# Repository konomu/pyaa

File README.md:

# Introducing pyaa!
A thirty key steno keyboard powered by QMK firmware and Plover.

## How do I build it?
To build pyaa, all you need is the following:
* PCB (two halves)
* 30 Kailh Choc switches (PG1350)
* 2 Pro Micros (or its derivatives)
  * **Important:** The Pro Micro's USB must face towards the board on both halves.
* 2 TRRS jacks (MJ-4PP-9 or PJ-320A)
* TRRS cable
* and optionally, 2 reset switches (TVBP06)

Once you have finished building it, you must flash the firmware onto the keyboard with QMK.

## How do I use it?
pyaa is powered by QMK firmware and takes advantage of its stenography, combo, and direct pin implementations. Its firmware is available [here](https://github.com/konomu/qmk_firmware/tree/pyaa/keyboards/pyaa). It functions along with [Plover](https://github.com/openstenoproject/plover), a desktop application developed as a part of the [Open Steno Project](http://www.openstenoproject.org/). 

## About
There are many other steno keyboards out there, all of which allow you to input text at speeds upwards of 200 words per minute with the magic of Plover! (and of course, a bit of practice) In fact, pyaa is heavily inspired by Georgi, which was developed by g Heavy Industries' Jane Bernhardt and is available at [gboards](https://www.gboards.ca/product/georgi). Other options for steno keyboards can be found on [Plover's wiki](https://github.com/openstenoproject/plover/wiki/Supported-Hardware).

The PCB uses a direct pin matrix, where each key is connected to an I/O pin on the microcontroller and ground. This makes it so that soldering diodes onto the pcb is not necessary as with other keyboards, reducing cost slightly. N-key rollover functionality, which is crucial for stenography, is left intact.

## Images

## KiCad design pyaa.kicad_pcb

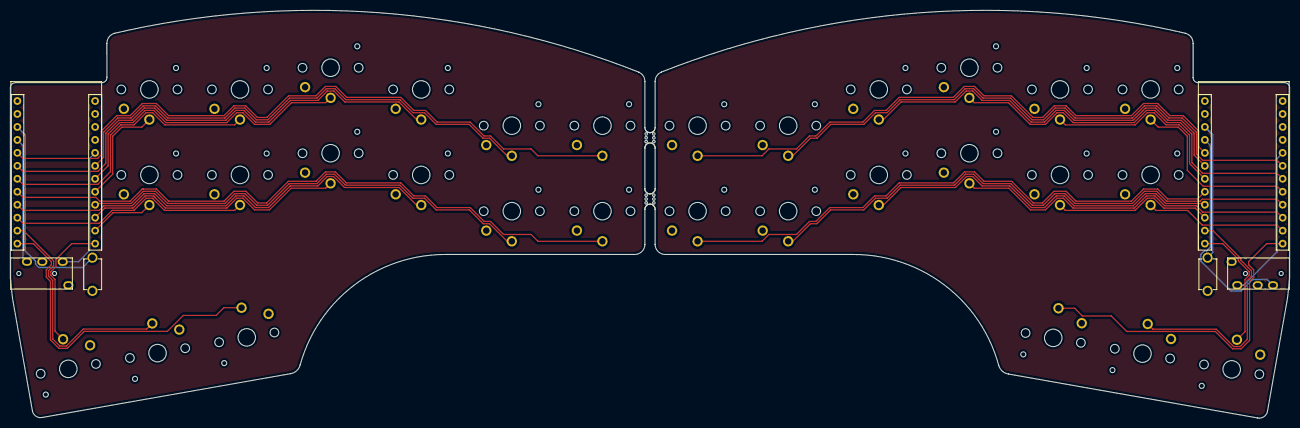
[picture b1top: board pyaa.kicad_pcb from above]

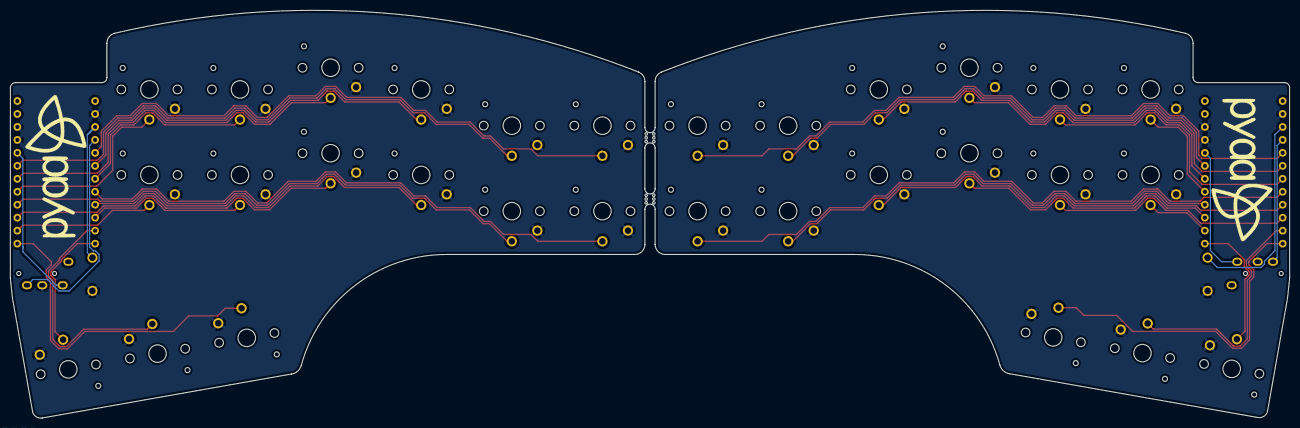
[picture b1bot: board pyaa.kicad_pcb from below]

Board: 2 copper layers, 250.6 x 79.9 mm, 38 parts (2 on the bottom side), 36 nets.

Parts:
J1, J2: MJ-4PP-9; TRRS-PJ-320A
K0, K1: KEYSW; Choc_PG1350_Choc_Spacing
KA1: KEYSW; Choc_PG1350_Choc_Spacing
KBR1: KEYSW; Choc_PG1350_Choc_Spacing
KDR1: KEYSW; Choc_PG1350_Choc_Spacing
KER1: KEYSW; Choc_PG1350_Choc_Spacing
KFR1: KEYSW; Choc_PG1350_Choc_Spacing
KGR1: KEYSW; Choc_PG1350_Choc_Spacing
KHL1: KEYSW; Choc_PG1350_Choc_Spacing
KKL1: KEYSW; Choc_PG1350_Choc_Spacing
KLR1: KEYSW; Choc_PG1350_Choc_Spacing
KN1, KN2: KEYSW; Choc_PG1350_Choc_Spacing
KO1: KEYSW; Choc_PG1350_Choc_Spacing
KPL1: KEYSW; Choc_PG1350_Choc_Spacing
KPR1: KEYSW; Choc_PG1350_Choc_Spacing
KRL1: KEYSW; Choc_PG1350_Choc_Spacing
KRR1: KEYSW; Choc_PG1350_Choc_Spacing
KSL1, KSL2: KEYSW; Choc_PG1350_Choc_Spacing
KSR1: KEYSW; Choc_PG1350_Choc_Spacing
KST1, KST2, KST3, KST4: KEYSW; Choc_PG1350_Choc_Spacing
KTL1: KEYSW; Choc_PG1350_Choc_Spacing
KTR1: KEYSW; Choc_PG1350_Choc_Spacing
KUR1: KEYSW; Choc_PG1350_Choc_Spacing
KWL1: KEYSW; Choc_PG1350_Choc_Spacing
KZR1: KEYSW; Choc_PG1350_Choc_Spacing
SW1, SW2: SW_PUSH; TACT_SWITCH_TVBP06
U1, U2: ProMicro; ProMicro_rev
mouse-bite-2mm-slot, mouse-bite-2mm-slot#2: VAL**; mouse-bite-2mm-slot

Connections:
GND: J1.R2, J2.R2, K0.2, K1.2, KA1.2, KBR1.2, KDR1.2, KER1.2, KFR1.2, KGR1.2, KHL1.2, KKL1.2, KLR1.2, KN1.2, KN2.2, KO1.2, KPL1.2, KPR1.2, KRL1.2, KRR1.2, KSL1.2, KSL2.2, KSR1.2, KST1.2, KST2.2, KST3.2, KST4.2, KTL1.2, KTR1.2, KUR1.2, KWL1.2, KZR1.2, SW1.2, SW2.2, U1.3, U1.4, U1.23, U2.3, U2.4, U2.23
unnamed: J1.S, U1.5
unnamed: J2.S, U2.5
unnamed: K0.1, U1.20
unnamed: K1.1, U1.17
unnamed: KA1.1, U1.14
unnamed: KBR1.1, U2.10
unnamed: KDR1.1, U2.20
unnamed: KER1.1, U2.13
unnamed: KFR1.1, U2.18
unnamed: KGR1.1, U2.16
unnamed: KHL1.1, U1.18
unnamed: KKL1.1, U1.16
unnamed: KLR1.1, U2.19
unnamed: KN1.1, U1.13
unnamed: KN2.1, U2.12
unnamed: KO1.1, U1.12
unnamed: KPL1.1, U1.7
unnamed: KPR1.1, U2.7
unnamed: KRL1.1, U1.15
unnamed: KRR1.1, U2.15
unnamed: KSL1.1, U1.6
unnamed: KSL2.1, U1.9
unnamed: KSR1.1, U2.9
unnamed: KST1.1, U1.8
unnamed: KST2.1, U1.11
unnamed: KST3.1, U2.8
unnamed: KST4.1, U2.11
unnamed: KTL1.1, U1.19
unnamed: KTR1.1, U2.6
unnamed: KUR1.1, U2.14
unnamed: KWL1.1, U1.10
unnamed: KZR1.1, U2.17
unnamed: SW1.1, U1.22
unnamed: SW2.1, U2.22
VDD: J1.R1, J2.R1, U1.21, U2.21

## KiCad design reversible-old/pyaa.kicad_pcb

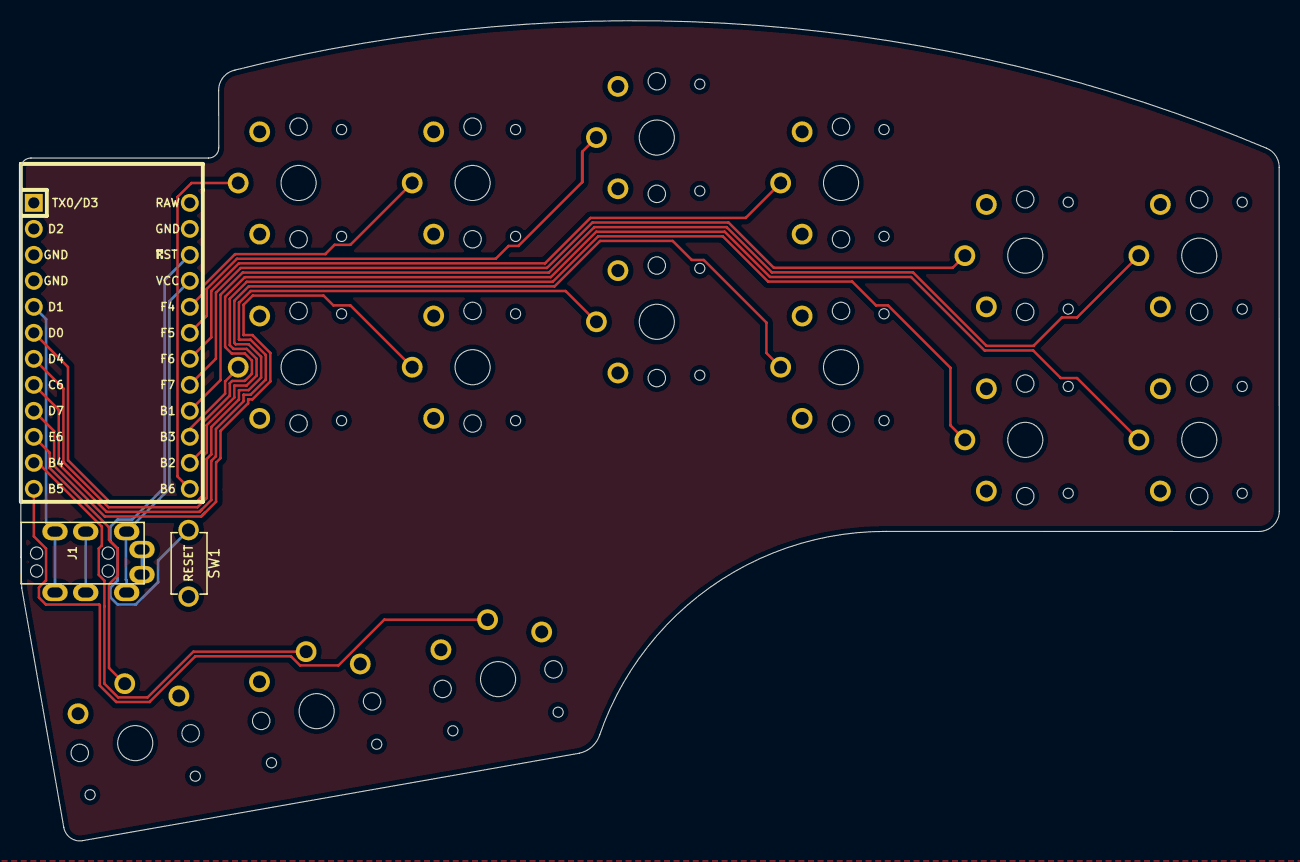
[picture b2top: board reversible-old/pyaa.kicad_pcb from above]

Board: 2 copper layers, 123.0 x 80.1 mm, 18 parts (0 on the bottom side), 19 nets.

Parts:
J1: MJ-4PP-9; MJ-4PP-9_rev2
K0, K1: KEYSW; Choc_PG1350_Choc_Spacing_Reversible
KA1: KEYSW; Choc_PG1350_Choc_Spacing_Reversible
KHL1: KEYSW; Choc_PG1350_Choc_Spacing_Reversible
KKL1: KEYSW; Choc_PG1350_Choc_Spacing_Reversible
KN1: KEYSW; Choc_PG1350_Choc_Spacing_Reversible
KO1: KEYSW; Choc_PG1350_Choc_Spacing_Reversible
KPL1: KEYSW; Choc_PG1350_Choc_Spacing_Reversible
KRL1: KEYSW; Choc_PG1350_Choc_Spacing_Reversible
KS1, KS2: KEYSW; Choc_PG1350_Choc_Spacing_Reversible
KST1, KST2: KEYSW; Choc_PG1350_Choc_Spacing_Reversible
KTL1: KEYSW; Choc_PG1350_Choc_Spacing_Reversible
KWL1: KEYSW; Choc_PG1350_Choc_Spacing_Reversible
SW1: SW_PUSH; TACT_SWITCH_TVBP06
U1: ProMicro; ArduinoProMicro

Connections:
GND: J1.C, K0.2, K1.2, KA1.2, KHL1.2, KKL1.2, KN1.2, KO1.2, KPL1.2, KRL1.2, KS1.2, KS2.2, KST1.2, KST2.2, KTL1.2, KWL1.2, SW1.2, U1.3, U1.4, U1.23
unnamed: J1.B, U1.5
unnamed: K0.1, U1.16
unnamed: K1.1, U1.14
unnamed: KA1.1, U1.11
unnamed: KHL1.1, U1.20
unnamed: KKL1.1, U1.7
unnamed: KN1.1, U1.12
unnamed: KO1.1, U1.10
unnamed: KPL1.1, U1.19
unnamed: KRL1.1, U1.9
unnamed: KS1.1, U1.17
unnamed: KS2.1, U1.6
unnamed: KST1.1, U1.13
unnamed: KST2.1, U1.15
unnamed: KTL1.1, U1.18
unnamed: KWL1.1, U1.8
unnamed: SW1.1, U1.22
VDD: J1.D, U1.21

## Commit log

2021-04-11 Added project files
2021-04-11 Gerber files
2021-04-11 Add pictures
2021-04-26 update files
2021-04-26 move to sub
2021-04-26 Rename pyaa-cache.lib to v2/pyaa-cache.lib
2021-04-26 Rename v2/silkscreen.pretty/flora.kicad_mod to v2/silkscreen.pretty/fp/flora.kicad_mod
2025-02-12 Update README.md add image
